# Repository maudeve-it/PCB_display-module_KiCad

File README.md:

<br><br>

_**Piu' sotto, al termine della lingua inglese trovi il testo in italiano </i>**_

<br><br>

# Display Module PCB (KiCad)

Here are all the files about the KiCad wiring diagram and the PCB design for the display module of "The GSM Gate Opener".

I included also library for shematics and footprints for two new-designed items but they are not used in this module. Refer to https://github.com/maudeve-it/PCB_base-module_KiCad

File details:
- file ".mod" are footprint scheme and should be edited/imported via footprint editor
- file "000_* " are related to the EEschema library of the new items
- there's a ".png" file shown in this page
- all the other files are related to the KiCad project

---
> The software, schemes and PCB designs in this set of repositories are provided just for 
> illustrative purposes, sharing the personal experience on this project. 
> The software and design artifacts are provided as-is without any mantainence and without
> warranty of any kind. There is no guarantee of fitness for any particular application, 
> and no guarantee of completeness and correctness. 
> By downloading and using these materials the user accepts all risks associated with the
> construction and use of the circuits and devices described in these design files.

---

---

<br>
<br>

# PCB Modulo Base (KiCad)

Qui trovi tutti i file che occorrono alla apertura/editazione dello schema Kicad e del progetto KiCad della PCB relativa al modulo Display.

Ho incluso anche due librerie personalizzate contenenti lo schema e l'impronta PCB di nue nuovi articoli, anche se non utilizzati in questa parte del progetto. Fare riferimento a https://github.com/maudeve-it/PCB_base-module_KiCad

Dettagli sui file:
- i file ".mod" sono schemi delle impronte e dovrebbero essere usati con l'editor impronte per importarli nel progetto
- i file "000_* " sono la libreria EEschema degli schemi creati e da usare nel progetto
- C'e' un file ".png" con l'immagine mostrata in questa pagina
- tutti gli altri file vanno nella cartella di progetto KiCad

---
> Il software e gli schemi di progetto come i layout PCB in questa serie di repository 
> sono messe a disposizione con puro intento illustrativo e di condivisione dell'esperienza fatta
> Il software and gli elementi del progetto sono messi a disposizione "allo stato in cui sono"
> senza impegno di manutenzione e senza garanzie di alcun tipo. Piu' esplicitamente, non c'e' garanzia di 
> adeguatezza a soddisfare specifiche esigenze, ne di completezza o correttezza di alcuna parte.
> Scaricando ed utilizzando questo materiale l'utilizzatore accetta il rischio associato alla
> realizzazione ed all'utilizzo del circuito e dei componenti descritti in questi file.

---

---

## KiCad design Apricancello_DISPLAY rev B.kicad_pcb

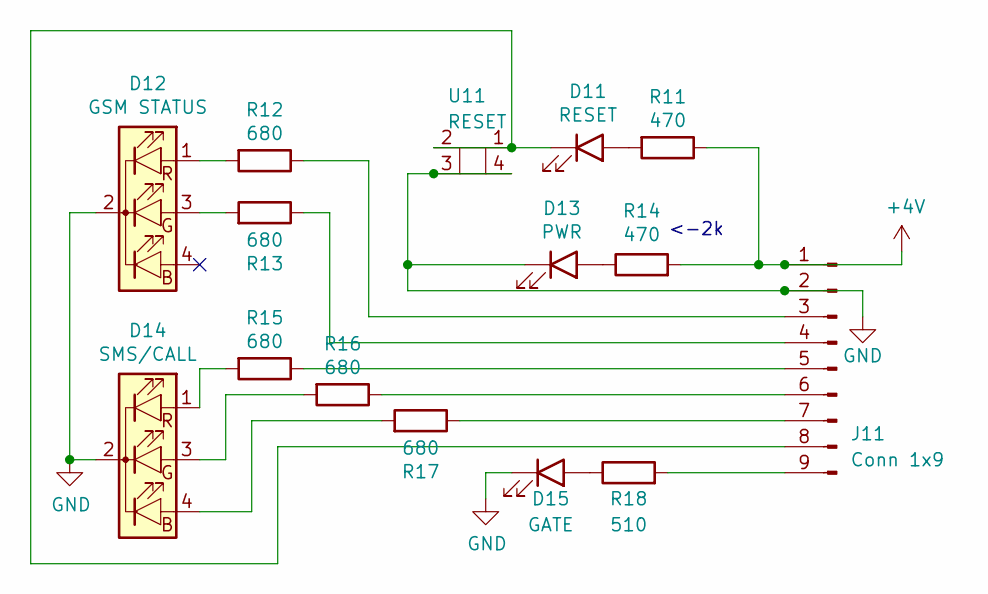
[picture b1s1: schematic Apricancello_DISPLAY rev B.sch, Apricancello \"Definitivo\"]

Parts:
D11: RESET; LED_D5.0mm
D12: GSM STATUS; LED_D5.0mm-4_RGB_Wide_Pins
D13: PWR; LED_D5.0mm
D14: SMS/CALL; LED_D5.0mm-4_RGB_Wide_Pins
D15: GATE; LED_D5.0mm
J11: Conn 1x9; PinHeader_1x09_P2.54mm_Vertical
R11, R14: 470; R_Axial_DIN0309_L9.0mm_D3.2mm_P12.70mm_Horizontal
R12, R13, R15, R16, R17: 680; R_Axial_DIN0309_L9.0mm_D3.2mm_P12.70mm_Horizontal
R18: 510; R_Axial_DIN0309_L9.0mm_D3.2mm_P12.70mm_Horizontal
U11: RESET; pulsante

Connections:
+4V: J11.1, R11.1, R14.2
GND: D12.2 (K), D13.1 (K), D14.2 (K), D15.1 (K), J11.2, U11.3, U11.4
unnamed: D11.1 (K), J11.8, U11.1, U11.2 (1.272)
unnamed: D11.2 (A), R11.2
unnamed: D12.1 (RA), R12.2
unnamed: D12.3 (GA), R13.2
unnamed: D13.2 (A), R14.1
unnamed: D14.1 (RA), R15.2
unnamed: D14.3 (GA), R16.2
unnamed: D14.4 (BA), R17.2
unnamed: D15.2 (A), R18.1
unnamed: J11.3, R12.1
unnamed: J11.4, R13.1
unnamed: J11.5, R15.1
unnamed: J11.6, R16.1
unnamed: J11.7, R17.1
unnamed: J11.9, R18.2

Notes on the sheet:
<-2k

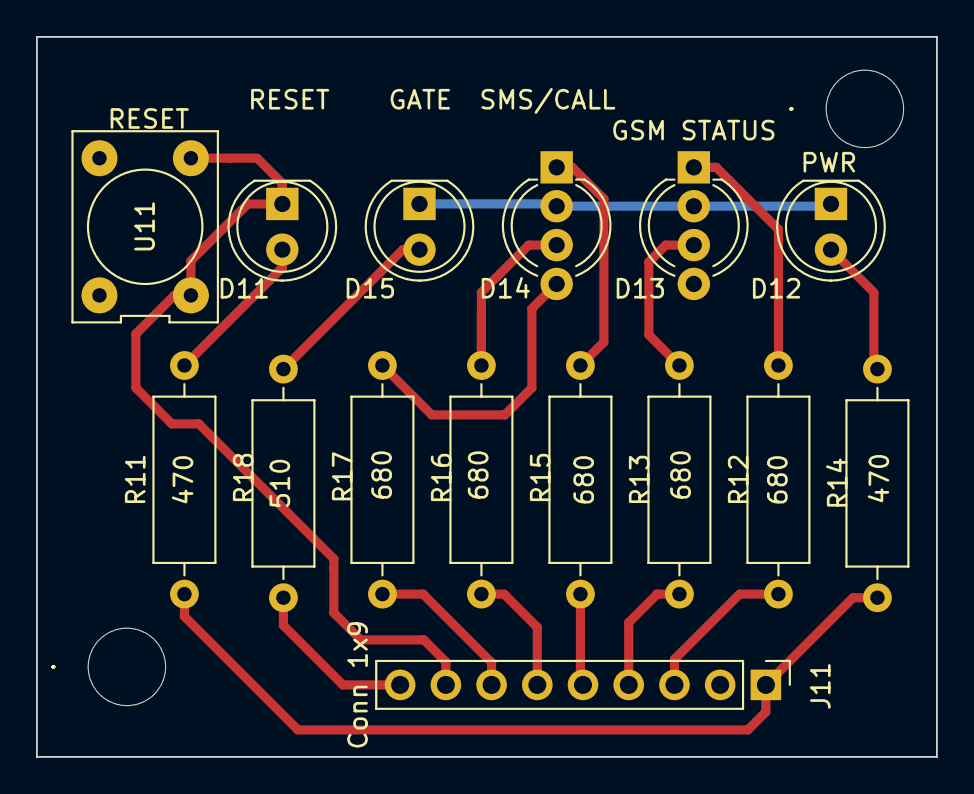
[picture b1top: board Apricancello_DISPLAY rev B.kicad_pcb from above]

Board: 2 copper layers, 50.0 x 40.0 mm, 17 parts (0 on the bottom side), 17 nets.

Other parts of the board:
., .#2: .; MountingHole_4.3mm_M4_ISO14580

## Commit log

2020-11-03 Create a
